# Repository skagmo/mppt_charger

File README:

MPPT charger
Jon Petter Skagmo, 2014
http://www.skagmo.com

The repository contains the following folders:
 - firmware:      MPLAB X project for the PIC microcontroller
 - datasheet:     Datasheets for (some) components on the PCB
 - pcb:           Eagle schematic and board
 - documentation: Relevant images/documentation
 - other:         Inspiration from others, articles, relevant material

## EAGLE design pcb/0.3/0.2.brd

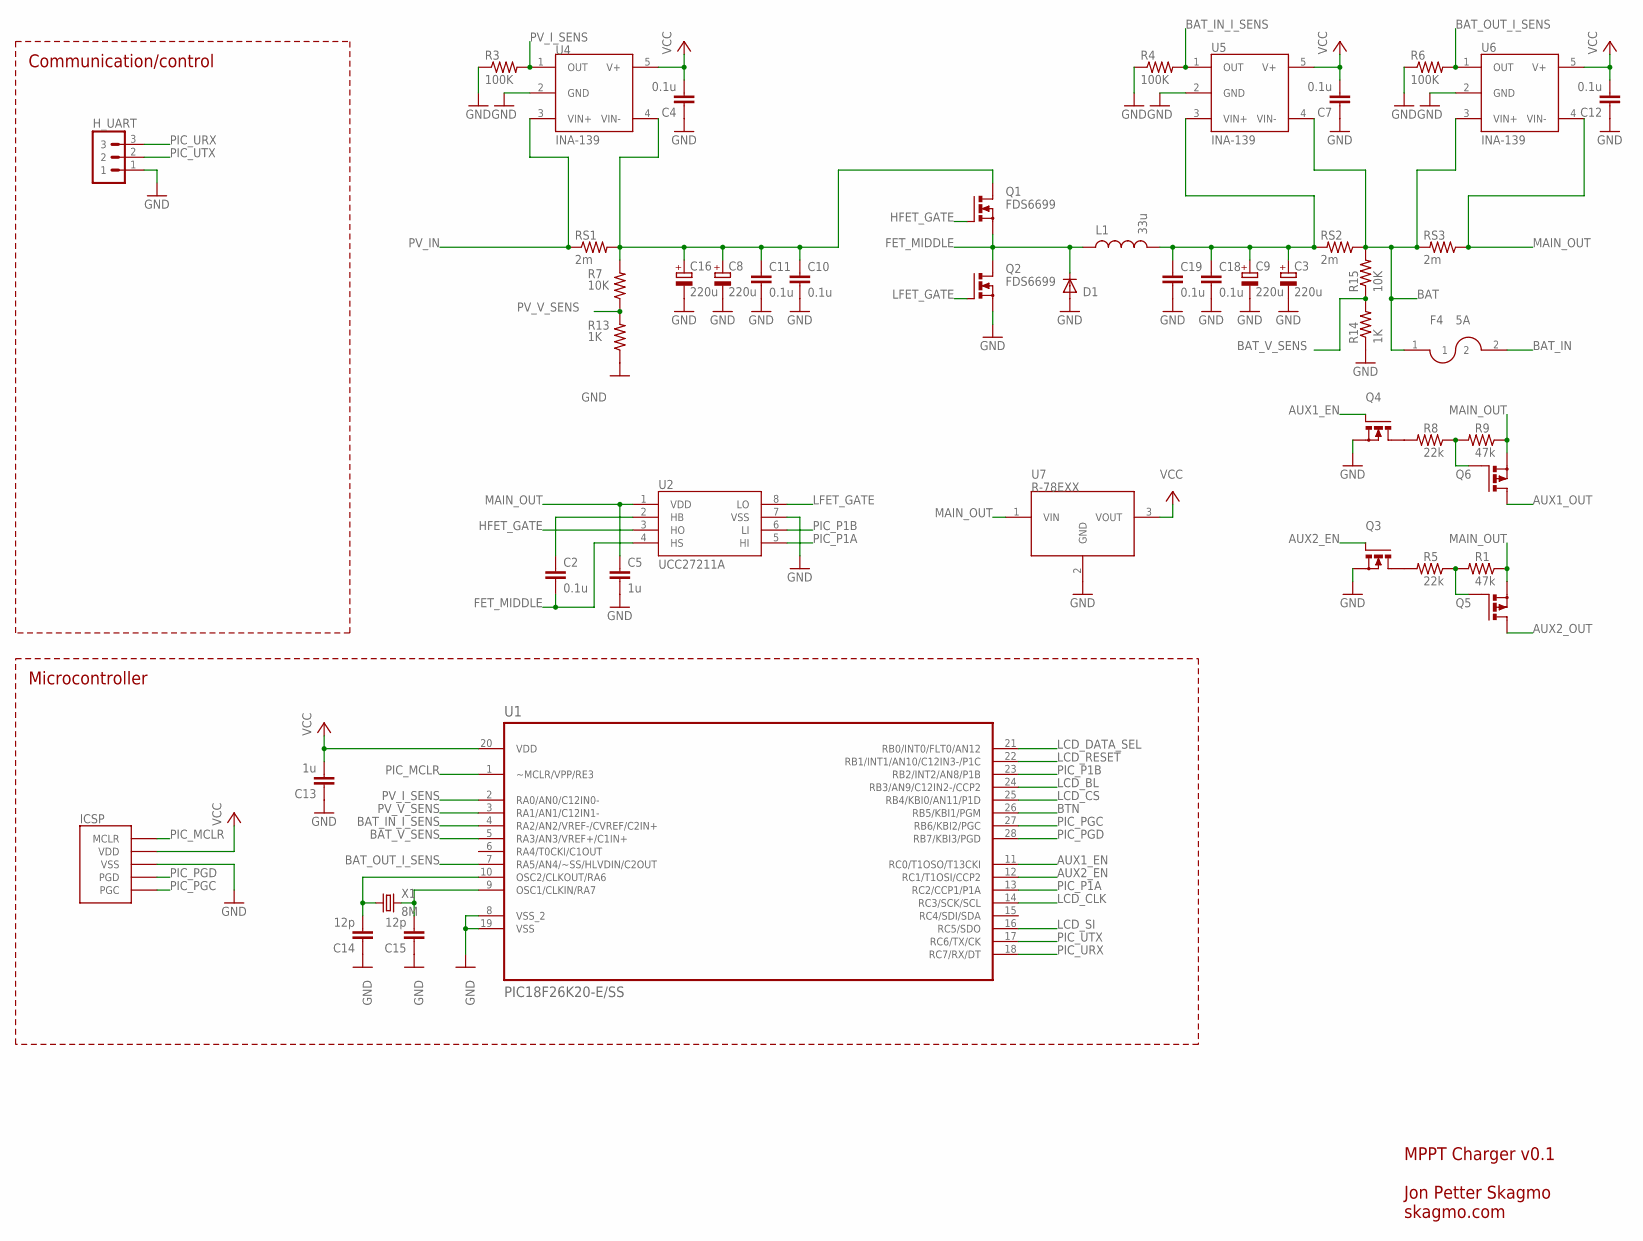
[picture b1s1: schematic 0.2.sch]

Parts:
C2, C4, C7, C10, C11, C12, C18, C19: 0.1u; 0603; PARTNO *
C3, C8, C9, C16: 220u; E3,5-8; PARTNO 35ZLH220MEFC8X11.5
C5, C13: 1u; 0603; PARTNO *
C14, C15: 12p; 0603; PARTNO *
D1: DIODESMB; SMB-DIODE; PARTNO SK54B-LTP
F4: 5A; 1206; PARTNO C1T 5
H_UART: H1X3_XH; CON_B3B-XH-A; PARTNO B3B-XH-A (LF)(SN)(P)
ICSP: 1X5_ICSP; 1X5_2MM; PARTNO *
L1: 33u; IHLP-6767; PARTNO IHLP6767GZER330M11
Q1, Q2: FDS6699; SO08; PARTNO SI4128DY-T1-GE3
Q3, Q4: MOSFET_N_SOT23-3; SOT23-3; PARTNO BSH103,215
Q5, Q6: PMOSFET_P; SO08; PARTNO FDS6681Z
R1, R9: 47k; 0603; PARTNO *
R3, R4, R6: 100K; 0603; PARTNO *
R5, R8: 22k; 0603; PARTNO *
R7, R15: 10K; 0603; PARTNO *
R13, R14: 1K; 0603; PARTNO *
RS1, RS2, RS3: 2m; R3225; PARTNO PMR25HZPFV2L00
U1: PIC18F26K20-E/SS; SOP65P780X200-28N; PARTNO PIC18F26K22-I/SS
U2: UCC27211A; SO08; PARTNO UCC27211D
U4, U5, U6: INA-139; SOT23-5; PARTNO INA139NA/250
U7: R-78EXX; PARTNO R-78E3.3-0.5
X1: 8M; TXC-7A; PARTNO 7A-8.000MAAE-T

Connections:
AUX1_EN: Q4.1 (G), U1.11 (RC0/T1OSO/T13CKI)
AUX1_OUT: Q6.5 (D), Q6.6 (D), Q6.7 (D), Q6.8 (D)
AUX2_EN: Q3.1 (G), U1.12 (RC1/T1OSI/CCP2)
AUX2_OUT: Q5.5 (D), Q5.6 (D), Q5.7 (D), Q5.8 (D)
BAT: F4.1, R15.2, RS2.1, RS3.2, U5.4 (VIN-), U6.3 (VIN+)
BAT_IN: F4.2
BAT_IN_I_SENS: R4.2, U1.4 (RA2/AN2/VREF-/CVREF/C2IN+), U5.1 (OUT)
BAT_OUT_I_SENS: R6.2, U1.7 (RA5/AN4/~SS/HLVDIN/C2OUT), U6.1 (OUT)
BAT_V_SENS: R14.2, R15.1, U1.5 (RA3/AN3/VREF+/C1IN+)
BTN: U1.26 (RB5/KBI1/PGM)
FET_MIDDLE: C2.2, D1.C, L1.P$1 (1), Q1.1 (S), Q1.2 (S), Q1.3 (S), Q2.5 (D), Q2.6 (D), Q2.7 (D), Q2.8 (D), U2.4 (HS)
GND: C3.-, C4.1, C5.2, C7.1, C8.-, C9.-, C10.2, C11.2, C12.1, C13.1, C14.1, C15.1, C16.-, C18.2, C19.2, D1.A, H_UART.1, ICSP.P$3 (VSS), Q2.1 (S), Q2.2 (S), Q2.3 (S), Q3.2 (S), Q4.2 (S), R3.1, R4.1, R6.1, R13.1, R14.1, U1.8 (VSS_2), U1.19 (VSS), U2.7 (VSS), U4.2 (GND), U5.2 (GND), U6.2 (GND), U7.2 (GND)
HFET_GATE: Q1.4 (G), U2.3 (HO)
LCD_BL: U1.24 (RB3/AN9/C12IN2-/CCP2)
LCD_CLK: U1.14 (RC3/SCK/SCL)
LCD_CS: U1.25 (RB4/KBI0/AN11/P1D)
LCD_DATA_SEL: U1.21 (RB0/INT0/FLT0/AN12)
LCD_RESET: U1.22 (RB1/INT1/AN10/C12IN3-/P1C)
LCD_SI: U1.16 (RC5/SDO)
LFET_GATE: Q2.4 (G), U2.8 (LO)
MAIN_OUT: C5.1, Q5.1 (S), Q5.2 (S), Q5.3 (S), Q6.1 (S), Q6.2 (S), Q6.3 (S), R1.1, R9.1, RS3.1, U2.1 (VDD), U6.4 (VIN-), U7.1 (VIN)
unnamed: C2.1, U2.2 (HB)
unnamed: Q3.3 (D), R5.2
unnamed: Q4.3 (D), R8.2
unnamed: C3.+, C9.+, C18.1, C19.1, L1.P$2 (2), RS2.2, U5.3 (VIN+)
unnamed: Q5.4 (G), R1.2, R5.1
unnamed: C14.2, U1.10 (OSC2/CLKOUT/RA6), X1.1
unnamed: Q6.4 (G), R8.1, R9.2
unnamed: C15.2, U1.9 (OSC1/CLKIN/RA7), X1.2
PIC_MCLR: ICSP.P$1 (MCLR), U1.1 (~MCLR/VPP/RE3)
PIC_P1A: U1.13 (RC2/CCP1/P1A), U2.5 (HI)
PIC_P1B: U1.23 (RB2/INT2/AN8/P1B), U2.6 (LI)
PIC_PGC: ICSP.P$5 (PGC), U1.27 (RB6/KBI2/PGC)
PIC_PGD: ICSP.P$4 (PGD), U1.28 (RB7/KBI3/PGD)
PIC_URX: H_UART.3, U1.18 (RC7/RX/DT)
PIC_UTX: H_UART.2, U1.17 (RC6/TX/CK)
PV: C8.+, C10.1, C11.1, C16.+, Q1.5 (D), Q1.6 (D), Q1.7 (D), Q1.8 (D), R7.2, RS1.2, U4.4 (VIN-)
PV_IN: RS1.1, U4.3 (VIN+)
PV_I_SENS: R3.2, U1.2 (RA0/AN0/C12IN0-), U4.1 (OUT)
PV_V_SENS: R7.1, R13.2, U1.3 (RA1/AN1/C12IN1-)
VCC: C4.2, C7.2, C12.2, C13.2, ICSP.P$2 (VDD), U1.20 (VDD), U4.5 (V+), U5.5 (V+), U6.5 (V+), U7.3 (VOUT)

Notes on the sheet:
MPPT Charger v0.1 Jon Petter Skagmo skagmo.com
Communication/control
Microcontroller

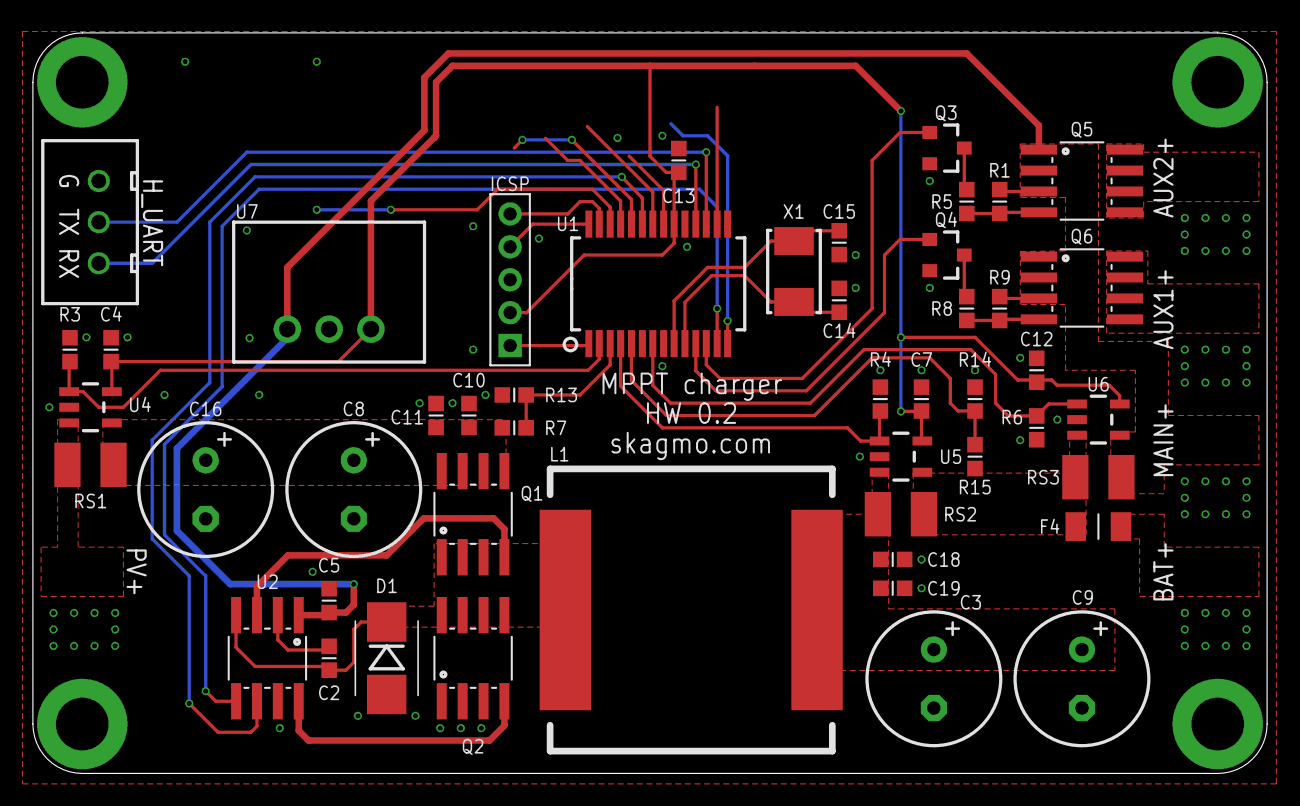
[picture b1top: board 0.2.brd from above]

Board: 4 copper layers, 75.0 x 45.0 mm, 48 parts (0 on the bottom side), 33 nets.

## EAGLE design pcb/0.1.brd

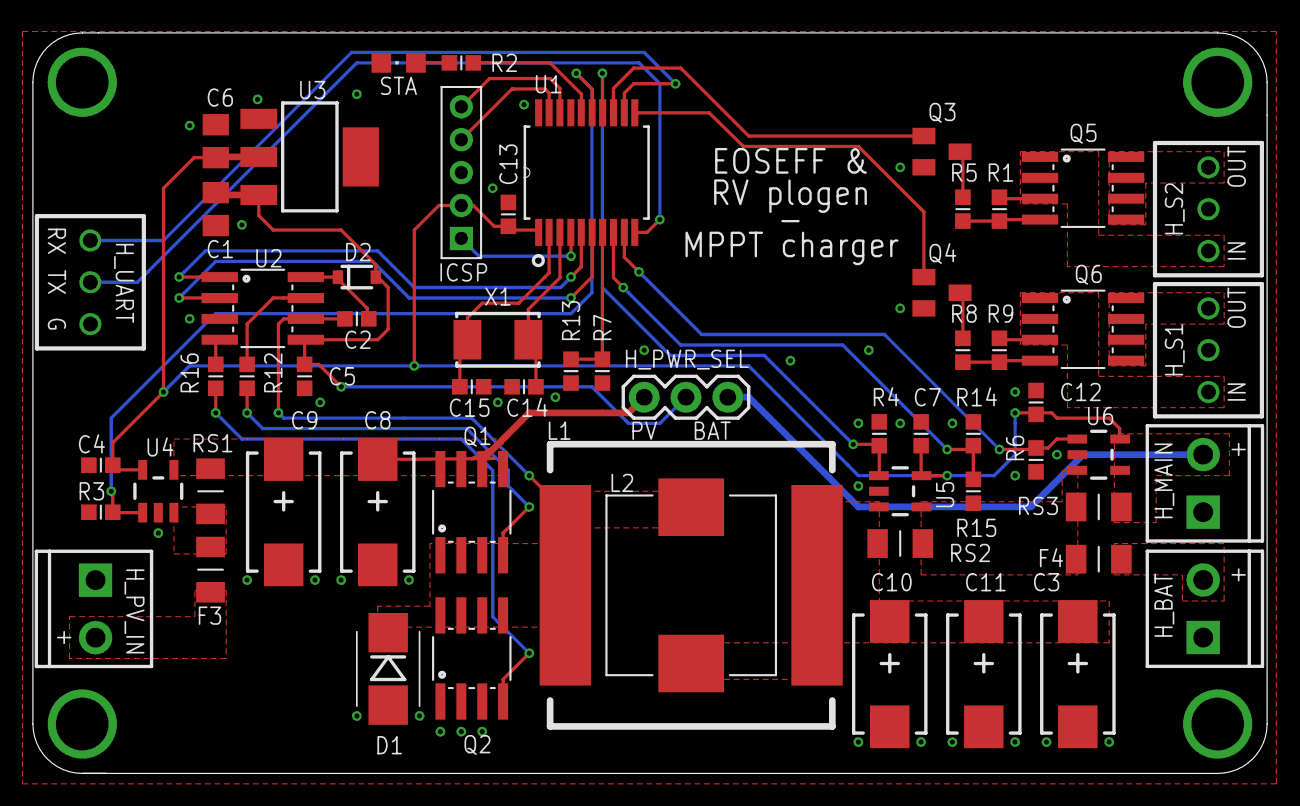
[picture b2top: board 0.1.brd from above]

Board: 4 copper layers, 75.0 x 45.0 mm, 64 parts (0 on the bottom side), 42 nets.

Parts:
C1, C6: 10u; C0805K
C2, C4, C7, C12: 0.1u; 0603
C3, C8, C9, C10, C11: 47u; CT7343
C5, C13: 1u; 0603
C14, C15: 0603
D1: SMB-DIODE
D2: DNI; SOD-323
F3, F4: 5A; 1206
H_BAT: SCREWTERMINAL-3.5MM-2
H_MAIN: SCREWTERMINAL-3.5MM-2
H_PV_IN: SCREWTERMINAL-3.5MM-2
H_PWR_SEL: 1X03
H_S1, H_S2: 1X3_SCREW_0.1
H_UART: 1X3_SCREW_0.1
ICSP: 1X5_ICSP; 1X5_2MM
L1: IHLP-6767
L2: IHLP-4040
Q1, Q2: FDS6699; SO08
Q3, Q4: BSS123; SOT23
Q5, Q6: SO08
R1, R5, R8, R9: 0603
R2: 220; 0603
R3, R4, R6: 100K; 0603
R7, R15: 10K; 0603
R12, R16: 0; 0603
R13, R14: 1K; 0603
RS1, RS2, RS3: 0.1; 1206
STA: CHIPLED_0805
U1: PIC18LF13K22-I/SS; SOP65P780X200-20N
U2: IR2183; SO08
U3: V_REG_317SMD; SOT223
U4, U5, U6: INA-139; SOT23-5
U$1, U$2, U$3, U$4: CORNER_SCREW
X1: TXC-7A

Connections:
$N100: F3.1, H_PV_IN.2
$N145: F3.2, RS1.2, U4.3
BAT: F4.1, R15.2, RS2.1, RS3.2, U5.4, U6.3
BAT_IN_I_SENS: R4.2, U1.14, U5.1
BAT_OUT_I_SENS: R6.2, U1.9, U6.1
BAT_V_SENS: R14.2, R15.1, U1.8
GND: C1.2, C3.-, C4.1, C5.1, C6.2, C7.1, C8.-, C9.-, C10.-, C11.-, C12.1, C13.1, C14.1, C15.1, D1.A, H_BAT.1, H_MAIN.1, H_PV_IN.1, H_S1.P$2, H_S2.P$2, H_UART.P$1, ICSP.P$3, Q2.1, Q2.2, Q2.3, Q3.2, Q4.2, R3.1, R4.1, R6.1, R13.1, R14.1, STA.C, U1.20, U2.3, U3.1, U4.2, U5.2, U6.2, U$1.P$1, U$2.P$1, U$3.P$1, U$4.P$1
MAIN_OUT: H_MAIN.2, H_PWR_SEL.1, RS3.1, U6.4
unnamed: Q3.1, U1.13
unnamed: C2.2, D1.C, L1.P$1, L2.1, Q1.1, Q1.2, Q1.3, Q2.5, Q2.6, Q2.7, Q2.8, U2.6
unnamed: R12.2, U2.7
unnamed: R16.2, U2.4
unnamed: C3.+, C10.+, C11.+, L1.P$2, L2.2, RS2.2, U5.3
unnamed: Q3.3, R5.2
unnamed: Q5.4, R1.2, R5.1
unnamed: Q4.3, R8.2
unnamed: Q1.4, R12.1
unnamed: R2.2, STA.A
unnamed: Q2.4, R16.1
unnamed: R2.1, U1.16
unnamed: F4.2, H_BAT.2
unnamed: C14.2, U1.3, X1.1
unnamed: Q6.4, R8.1, R9.2
unnamed: C15.2, U1.2, X1.2
unnamed: C2.1, D2.1, U2.8
unnamed: Q4.1, U1.11
PIC_MCLR: ICSP.P$1, U1.4
PIC_P1A: U1.5, U2.1
PIC_P1B: U1.6, U2.2
PIC_PGC: ICSP.P$5, U1.18
PIC_PGD: ICSP.P$4, U1.19
PIC_URX: H_UART.P$3, U1.12
PIC_UTX: H_UART.P$2, U1.10
PV_IN: C8.+, C9.+, H_PWR_SEL.3, Q1.5, Q1.6, Q1.7, Q1.8, R7.2, RS1.1, U4.4
PV_I_SENS: R3.2, U1.15, U4.1
PV_V_SENS: R7.1, R13.2, U1.7
S0_IN: H_S2.P$1, Q5.1, Q5.2, Q5.3, R1.1
S0_OUT: H_S2.P$3, Q5.5, Q5.6, Q5.7, Q5.8
S1_IN: H_S1.P$1, Q6.1, Q6.2, Q6.3, R9.1
S1_OUT: H_S1.P$3, Q6.5, Q6.6, Q6.7, Q6.8
SYS_PWR: C1.1, C5.2, D2.2, H_PWR_SEL.2, U2.5, U3.3
VCC: C4.2, C6.1, C7.2, C12.2, C13.2, ICSP.P$2, U1.1, U3.2, U4.5, U5.5, U6.5

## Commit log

2014-06-13 Removed some functions no longer used, added a few code comments, changed the file structure.
2016-06-23 Added PCB and firmware for v0.2
2016-06-23 Added .gitignore
2016-11-03 Fixed: Output not turning on after low voltage shutdown

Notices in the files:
parts and their libraries:
SparkFun: Licensing: CC v3.0 Share-Alike You are welcome to use this library for commercial purposes.
